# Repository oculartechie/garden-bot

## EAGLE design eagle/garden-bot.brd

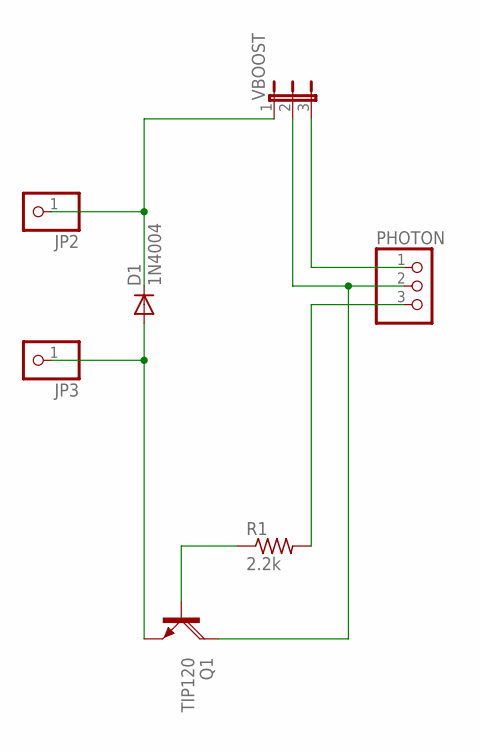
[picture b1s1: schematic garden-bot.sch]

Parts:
D1: 1N4004; DO41-10
JP2, JP3: PINHD-1X1; 1X01
PHOTON: PINHD-1X3; 1X03
Q1: TIP120; TO220AH
R1: 2.2k; 0207/10
VBOOST: JP2E; JP2

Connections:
D0: PHOTON.3, R1.2
GND: PHOTON.2, Q1.C, VBOOST.2
unnamed: Q1.B, R1.1
unnamed: D1.A, JP3.1, Q1.E
VCC: PHOTON.1, VBOOST.3
VOUT: D1.C, JP2.1, VBOOST.1

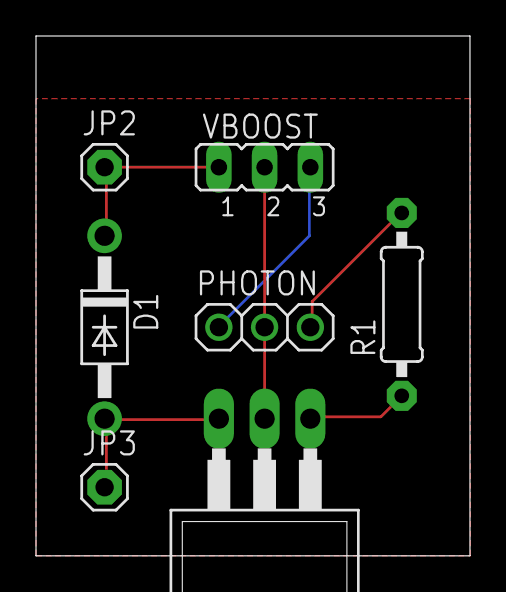
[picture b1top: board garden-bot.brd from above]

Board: 2 copper layers, 24.1 x 28.9 mm, 7 parts (0 on the bottom side), 6 nets.

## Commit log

2017-09-30 PCB for use with particle photon and solenoid valve
